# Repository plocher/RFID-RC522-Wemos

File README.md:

# RFID-RC522-Wemos
## License: CERN Open Hardware Licence v1.2

RFID reader based on RC522 module with Wemos and LCD

Initial version, talks rudamentary MQTT

I found a cheap RC522 RFID card reader on eBay [eBay example](https://www.ebay.com/i/112341068592)
and wanted to experiment with it.  In the future, I may
use this to do location-based interactions with the crews (i.e.,
switch list identification, local control unlocking, etc)

At this point, the Wemos D1 Mini can send MQTT messages via WiFi that can be
consumed by other nodes - or even JMRI.

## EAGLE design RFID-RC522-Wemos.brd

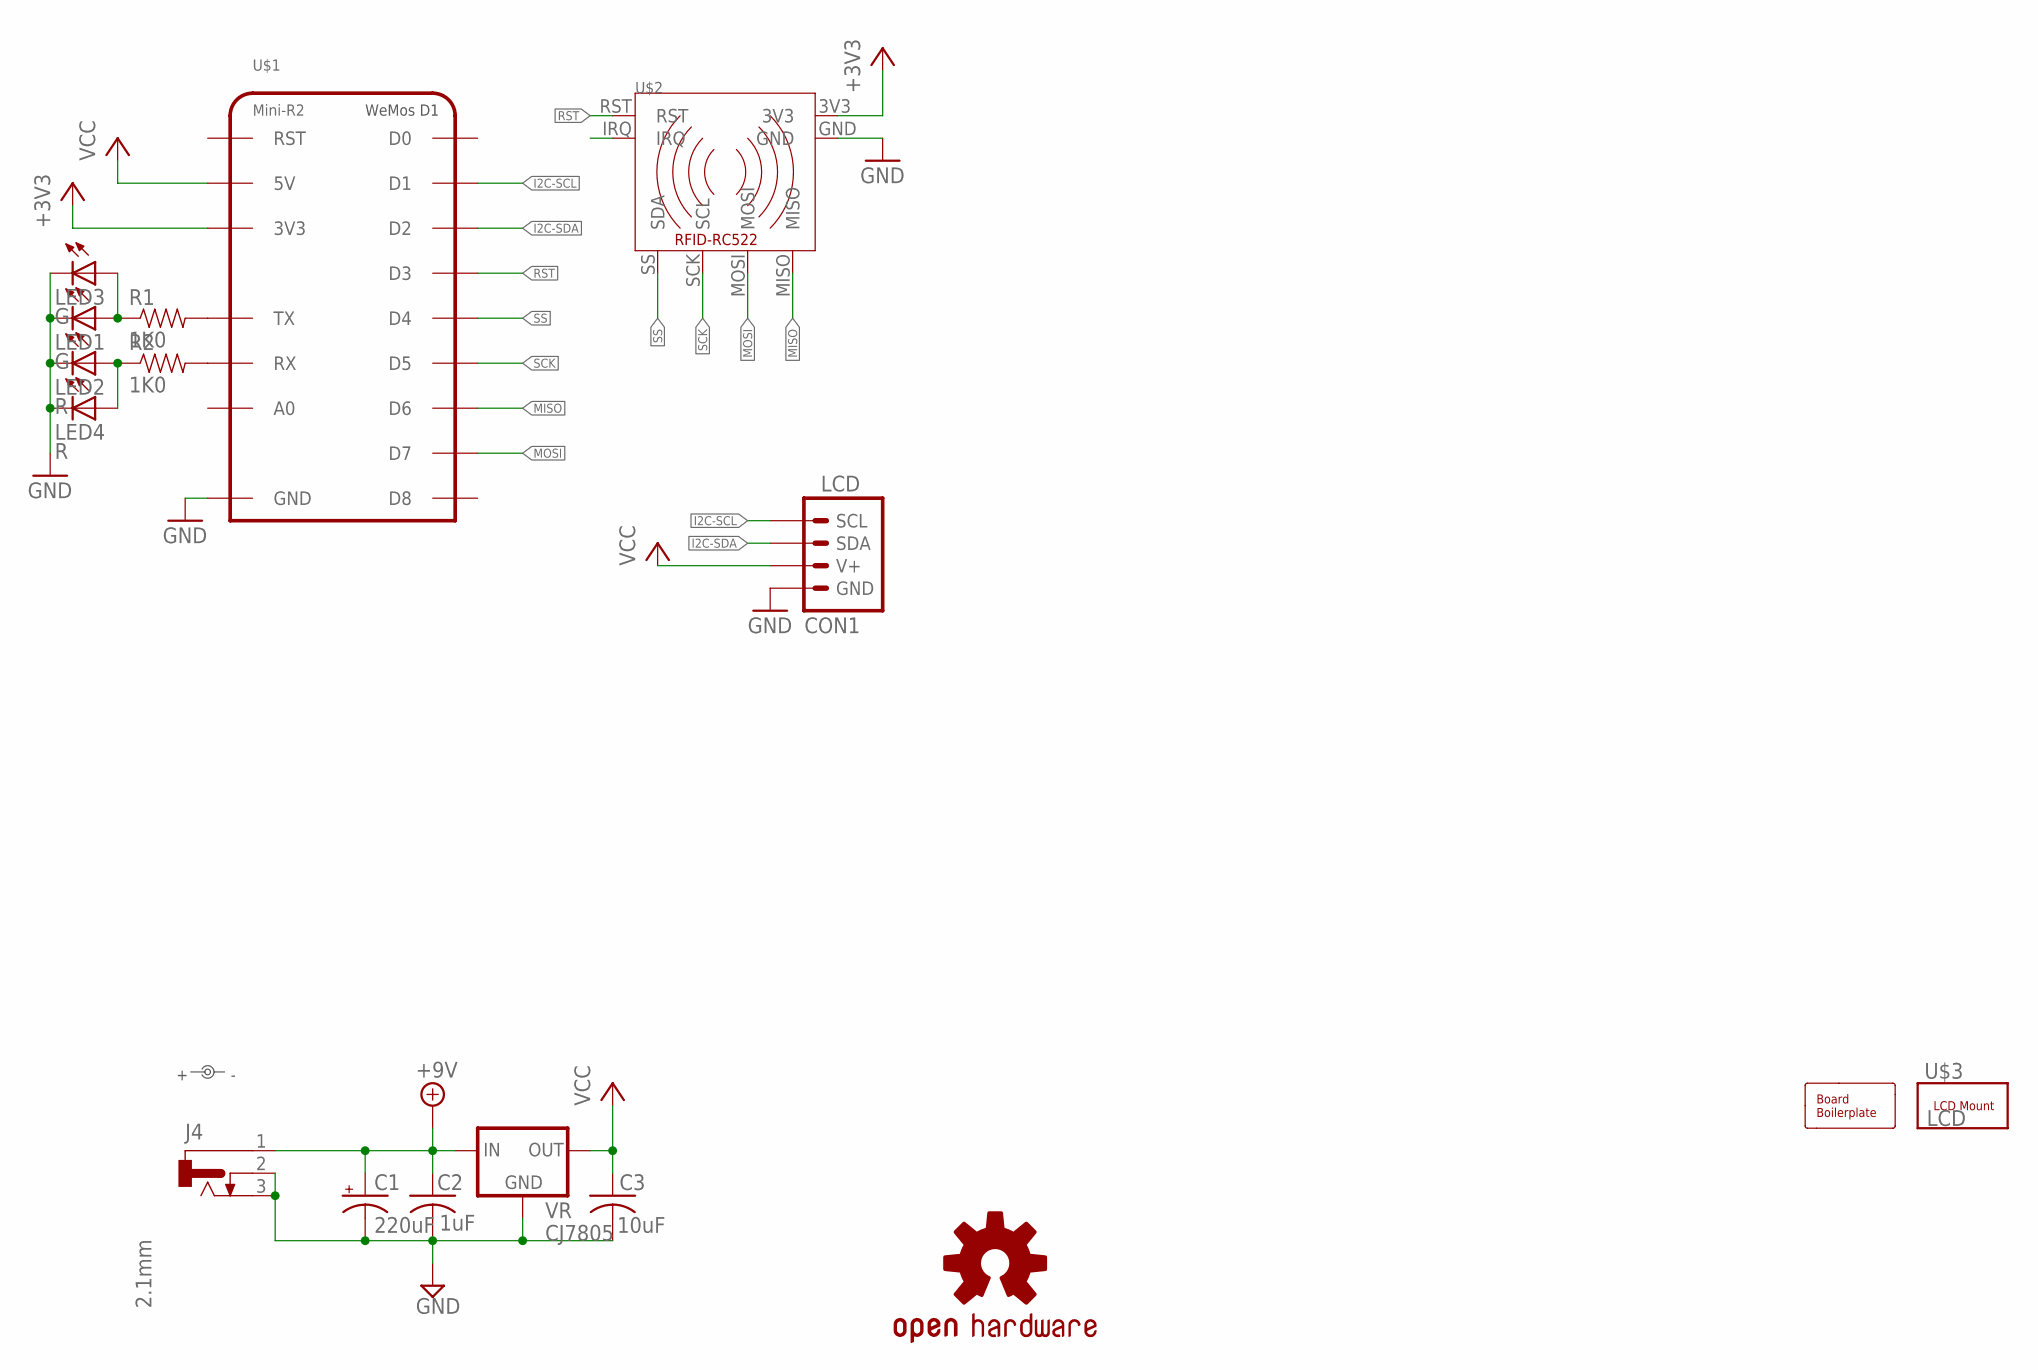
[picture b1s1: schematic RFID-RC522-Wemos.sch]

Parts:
BOARD1: 8x10; BOARD-DINRAIL-3.17INX10CM
C1: 220uF; 0810-CAP
C2: 1uF; 0603-CAP
C3: 10uF; 0603-CAP
CON1: LCD; I2C-L
J4: 2.1mm; DCJ0202
LED1: G; 0603-LED
LED2: R; 0603-LED
LED3: G; LED5MM
LED4: R; LED5MM
LOGO1: OSHW; OSHW-LOGO-L
POWER: 9-12vDC; PWR_LABEL
R1: 1K0; 0805-RES
R2: 1K0; 0603-RES
U$1: Mini-R2; WEMOS-D1
U$2: RFIDBACK; RC522-REVERSE
U$3: LCD; LCD-16X2-SILK
VR: CJ7805; TO-252

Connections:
+3V3: U$1.3V3, U$2.3V3
+9V: C1.+, C2.1, J4.1, VR.1 (IN)
GND: C1.-, C2.2, C3.2, CON1.GND, CON1.GND@1 (GND), J4.2, J4.3, LED1.C, LED2.C, LED3.K (C), LED4.K (C), U$1.GND, U$2.GND, VR.2 (GND)
I2C-SCL: CON1.SCL, CON1.SCL@1 (SCL), U$1.D1
I2C-SDA: CON1.SDA, CON1.SDA@1 (SDA), U$1.D2
MISO: U$1.D6, U$2.MISO
MOSI: U$1.D7, U$2.MOSI
unnamed: R1.2, U$1.TX
unnamed: R2.2, U$1.RX
unnamed: LED1.A, LED3.A, R1.1
unnamed: LED2.A, LED4.A, R2.1
RST: U$1.D3, U$2.RST
SCK: U$1.D5, U$2.SCK (SCL)
SS: U$1.D4, U$2.SS (SDA)
VCC: C3.1, CON1.V+, CON1.V+@1 (V+), U$1.5V, VR.3 (OUT)

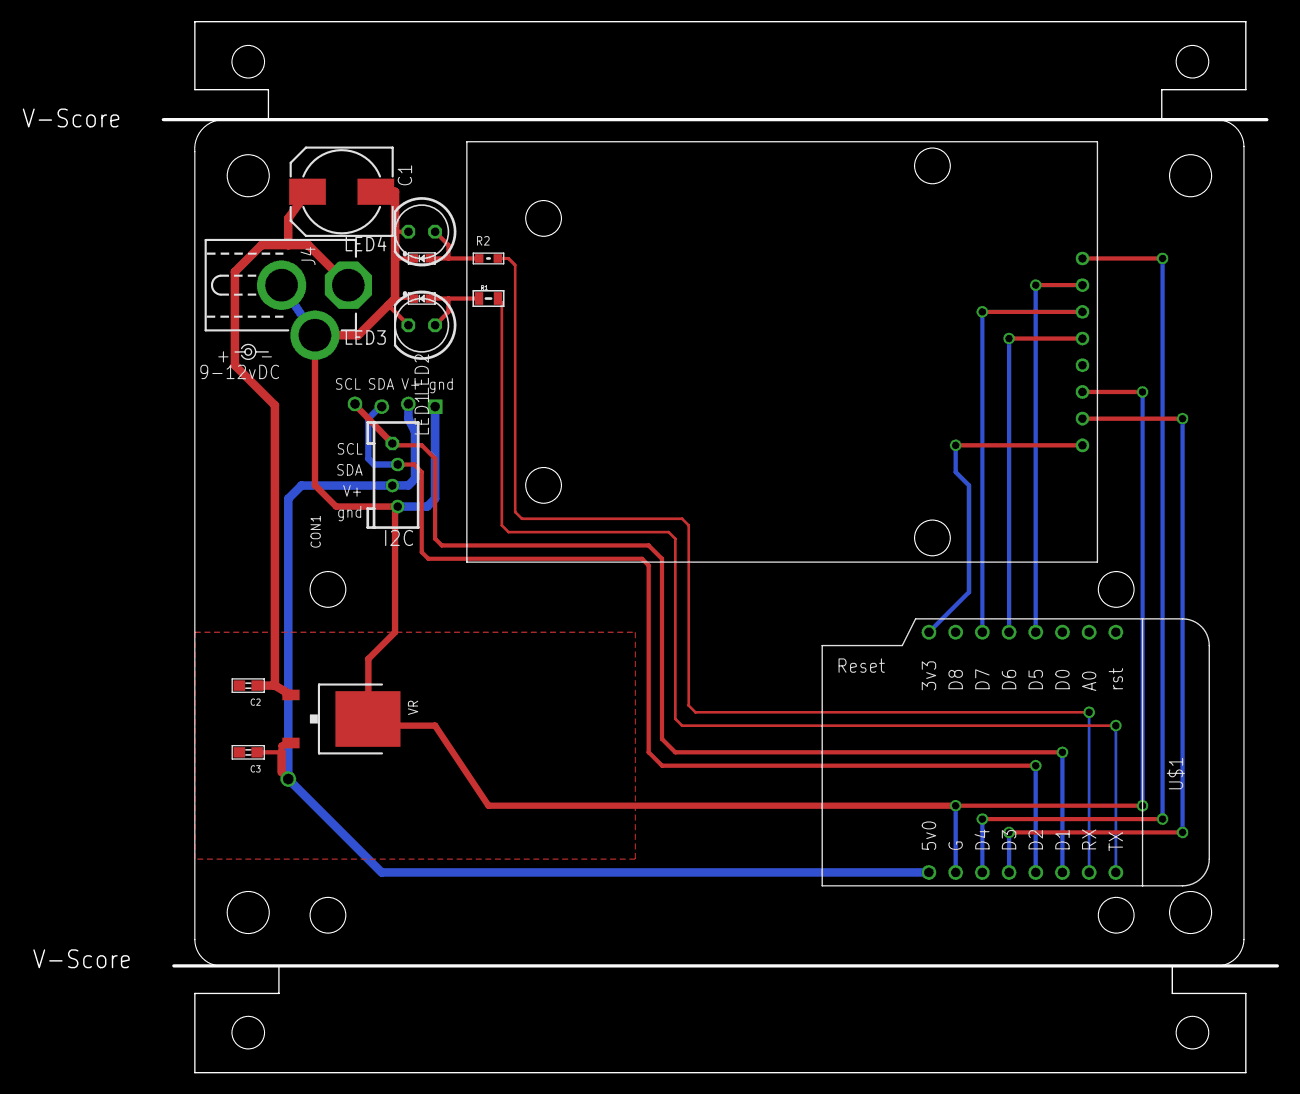
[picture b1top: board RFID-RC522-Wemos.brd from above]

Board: 2 copper layers, 106.0 x 100.0 mm, 18 parts (0 on the bottom side), 15 nets.

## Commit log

2019-12-09 added graphic
2020-05-04 updated tags
2020-10-05 added missing values
2020-10-06 normalized values

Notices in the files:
parts and their libraries:
SPCoast: Creative Commons - Attribution - ShareAlike 3.0
Other Rights—In no way are any of the following rights affected by the license:
your fair dealing or fair use rights;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
